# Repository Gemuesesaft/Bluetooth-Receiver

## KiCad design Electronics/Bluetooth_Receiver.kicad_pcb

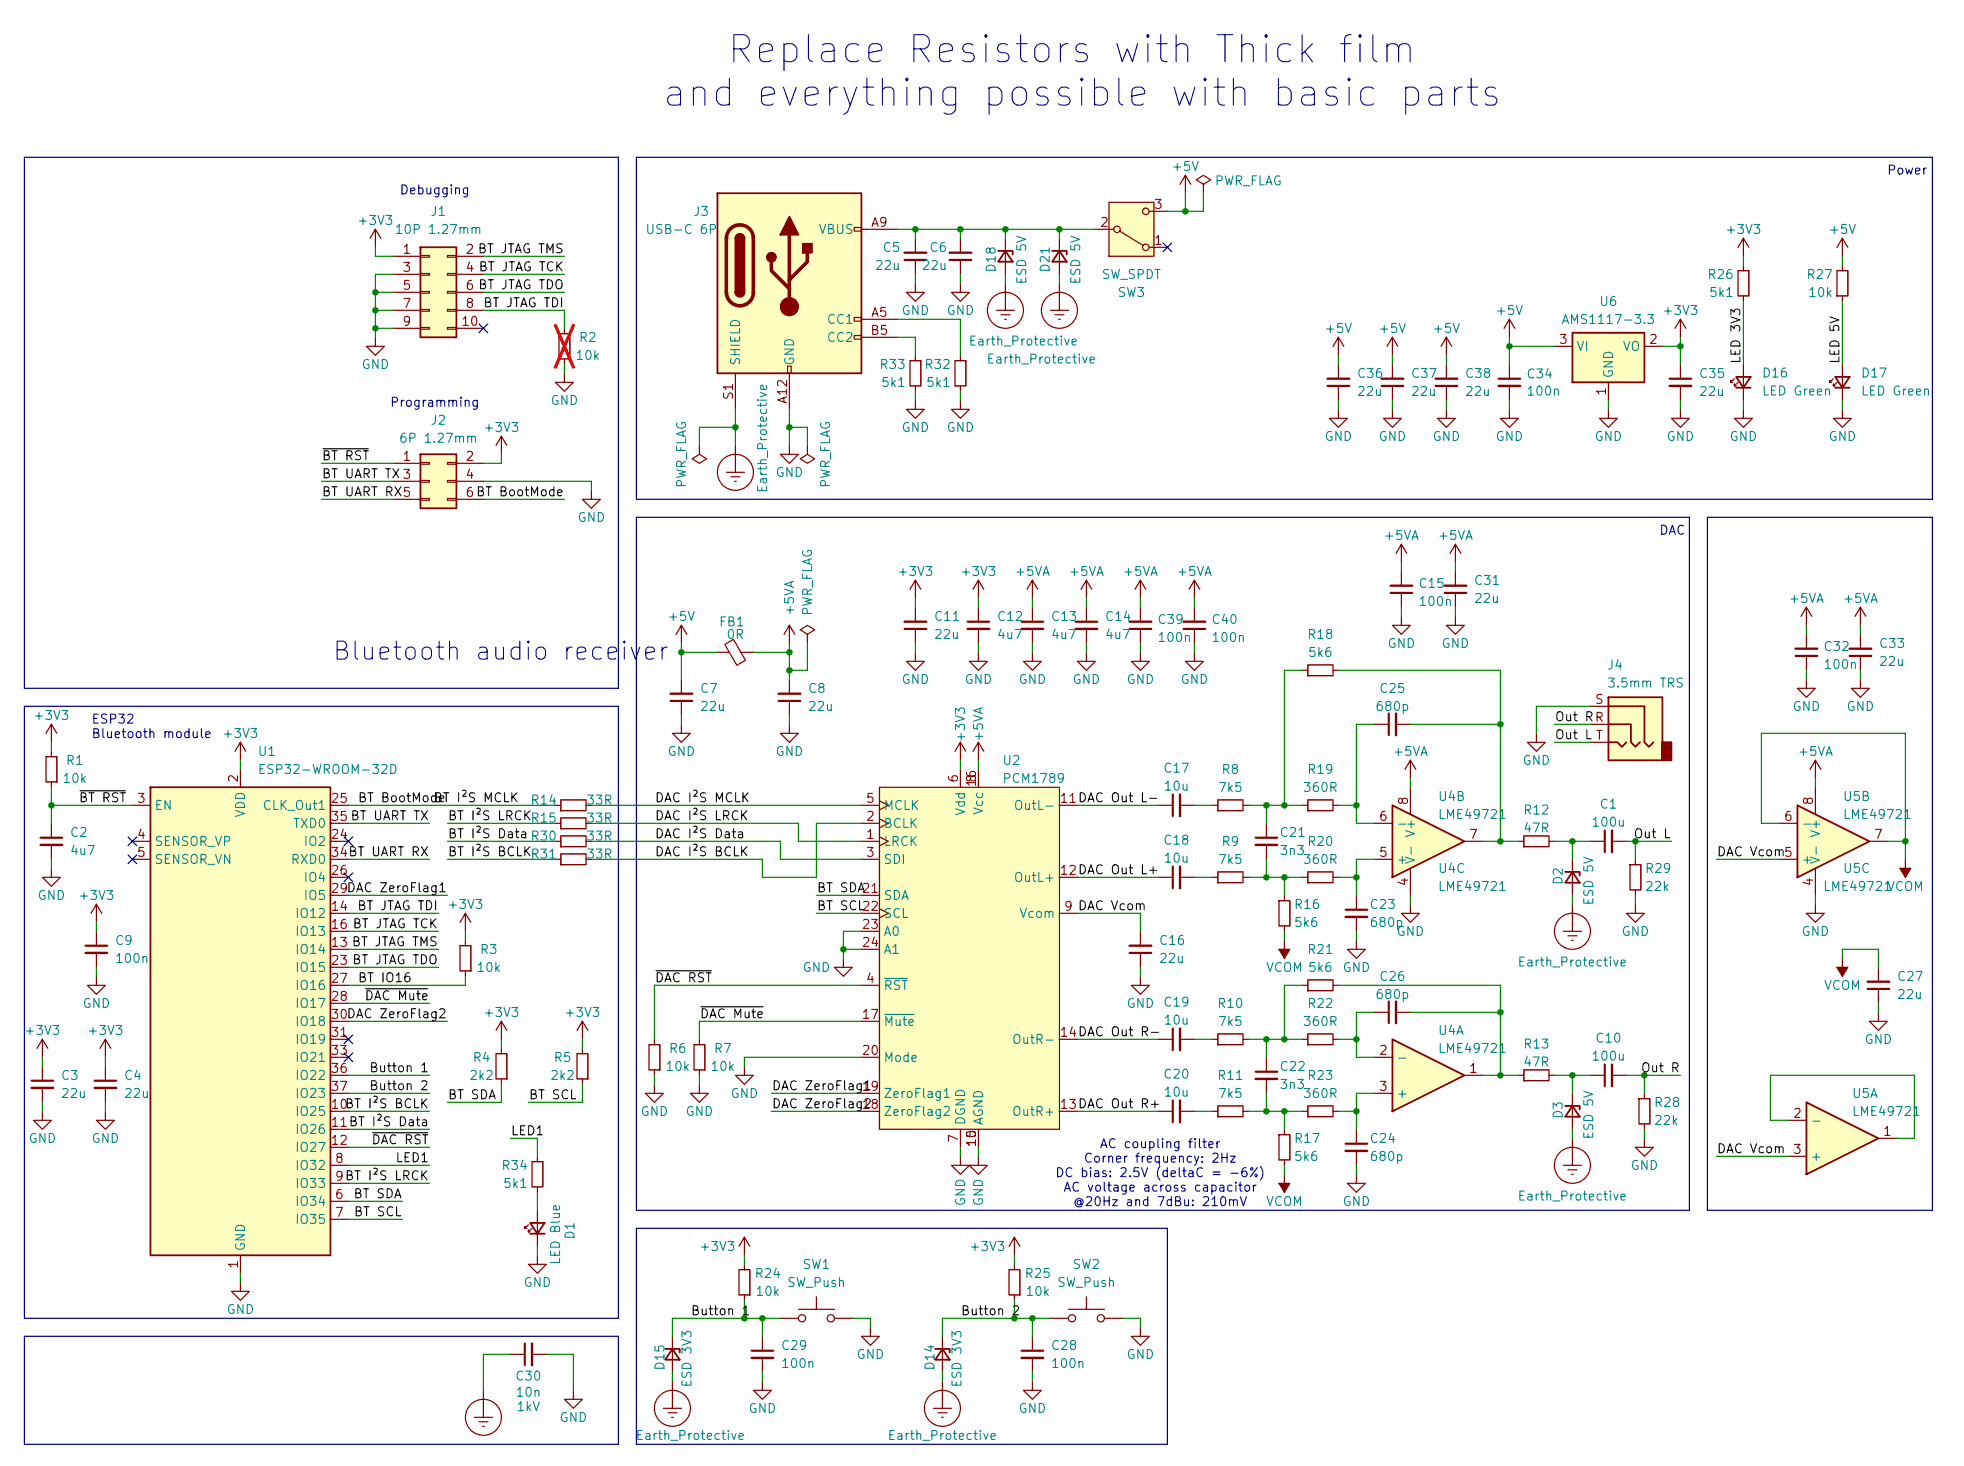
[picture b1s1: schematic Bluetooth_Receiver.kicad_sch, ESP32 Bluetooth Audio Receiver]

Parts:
C1, C10: 100u; C_1206_3216Metric; Rated Voltage 6V3; Tolerance 20%; Manufacturer Part # CL31A107MQHNNNE; JLCPCB Part # C15008
C2, C12, C13, C14: 4u7; C_0805_2012Metric; Rated Voltage 25V; Tolerance 10%; Manufacturer Part # CL21A475KAQNNNE; JLCPCB Part # C1779
C3, C4, C5, C6, C7, C8, C11, C16, C27, C31, C33, C35, C36, C37, C38: 22u; C_0805_2012Metric; Rated Voltage 25V; Tolerance 20%; Manufacturer Part # CL21A226MAQNNNE; JLCPCB Part # C45783
C9, C15, C28, C29, C32, C34, C39, C40: 100n; C_0603_1608Metric; Rated Voltage 50V; Tolerance 10%; Manufacturer Part # CC0603KRX7R9BB104; JLCPCB Part # C14663
C17, C18, C19, C20: 10u; C_1206_3216Metric; Rated Voltage 50V; Tolerance 10%; Manufacturer Part # CL31A106KBHNNNE; JLCPCB Part # C13585
C21, C22: 3n3; C_0603_1608Metric; Rated Voltage 50V; Tolerance 5%; Manufacturer Part # GRM1885C1H332JA01D; JLCPCB Part # C77036
C23, C24, C25, C26: 680p; C_0603_1608Metric; Rated Voltage 50V; Tolerance 5%; Manufacturer Part # CGA3E2C0G1H681JT0Y0N; JLCPCB Part # C342925
C30: 10n; C_1206_3216Metric; Rated Voltage 1kV; Manufacturer Part # 1206B103K102NT; JLCPCB Part # C9194
D1: LED Blue; LED_0805_2012Metric; Manufacturer Part # 17-21/BHC-AL2M2TY/3T; JLCPCB Part # C94613
D2, D3, D18, D21: ESD 5V; D_SOD-882; Manufacturer Part # ESD9X5.0ST5G-ES; JLCPCB Part # C19170850
D14, D15: ESD 3V3; D_SOD-523; Manufacturer Part # ESD5Z3.3; JLCPCB Part # C475684
D16, D17: LED Green; LED_0805_2012Metric; Manufacturer Part # KT-0805G; JLCPCB Part # C2297
FB1: 0R; L_0603_1608Metric; Tolerance 50mΩ; Manufacturer Part # 0603WAF0000T5E; JLCPCB Part # C21189
J1: 10P 1.27mm; PinHeader_2x05_P1.27mm_Horizontal; Manufacturer Part # 1271WR-2x5P; JLCPCB Part # C7470108
J2: 6P 1.27mm; PinHeader_2x03_P1.27mm_Horizontal; Manufacturer Part # 1271WR-2x3P; JLCPCB Part # C7470106
J3: USB-C 6P; USB_C_Receptacle_HRO_TYPE-C-31-M-17; Manufacturer Part # HC-TYPE-C-6P-01A; JLCPCB Part # C2894893
J4: 3.5mm TRS; Jack_3.5mm_CUI_SJ-3523-SMT_Horizontal; Manufacturer Part # PJ-320-3P SMT; JLC Basic Part No
R1, R3, R6, R7, R24, R25, R27: 10k; R_0402_1005Metric; Rated Voltage 50V; Tolerance 1%; Manufacturer Part # 0402WGF1002TCE; JLCPCB Part # C25744
R2: 10k; R_0402_1005Metric; Rated Voltage 50V; Tolerance 1%; Manufacturer Part # 0402WGF1002TCE; JLCPCB Part # C25744; not fitted
R4, R5: 2k2; R_0402_1005Metric; Rated Voltage 50V; Tolerance 1%; Manufacturer Part # 0402WGF2201TCE; JLCPCB Part # C25879
R8, R9, R10, R11: 7k5; R_0805_2012Metric; Rated Voltage 150V; Tolerance 0.1%; Manufacturer Part # RT0805BRD077K5L; JLCPCB Part # C136918
R12, R13: 47R; R_0805_2012Metric; Rated Voltage 150V; Tolerance 1%; Manufacturer Part # 0805W8F470JT5E; JLCPCB Part # C17714
R14, R15, R30, R31: 33R; R_0402_1005Metric; Rated Voltage 50V; Tolerance 1%; Manufacturer Part # 0402WGF330JTCE; JLCPCB Part # C25105
R16, R17, R18, R21: 5k6; R_0805_2012Metric; Rated Voltage 100V; Tolerance 0.1%; Manufacturer Part # ERA6AEB562V; JLCPCB Part # C445654
R19, R20, R22, R23: 360R; R_0805_2012Metric; Rated Voltage 150V; Tolerance 0.1%; Manufacturer Part # RT0805BRD07360RL; JLCPCB Part # C865427
R26, R32, R33, R34: 5k1; R_0603_1608Metric; Rated Voltage 50V; Tolerance 1%; Manufacturer Part # 0603WAF5101T5E; JLC Basic Part Yes
R28, R29: 22k; R_0402_1005Metric; Rated Voltage 50V; Tolerance 1%; Manufacturer Part # 0402WGF2202TCE; JLCPCB Part # C25768
SW1, SW2: SW_Push; SKMP; Manufacturer Part # SKPMBHE010; JLCPCB Part # C115350
SW3: SW_SPDT; SW_Slide-03_Wuerth-WS-SLTV_10x2.5x6.4_P2.54mm; Manufacturer Part # SS-12D01-G5; JLC Basic Part No
U1: ESP32-WROOM-32D; Manufacturer Part # ESP32-WROOM-32D-H4; JLCPCB Part # C3013936
U2: PCM1789; TSSOP-24_4.4x7.8mm_P0.65mm; Manufacturer Part # PCM1789PWR; JLCPCB Part # C962089
U4, U5: LME49721; SOIC-8_3.9x4.9mm_P1.27mm; Manufacturer Part # LME49721MAX/NOPB; JLCPCB Part # C129347
U6: AMS1117-3.3; SOT-223-3_TabPin2; Manufacturer Part # AMS1117-3.3; JLC Basic Part Yes

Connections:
+3V3: C3.1, C4.1, C9.1, C11.2, C12.1, C35.1, J1.1, J2.2, R1.2, R3.2, R4.2, R5.2, R24.2, R25.2, R26.1, U1.2 (VDD), U2.6 (Vdd), U6.2 (VO)
+5V: C7.2, C34.1, C36.2, C37.2, C38.2, FB1.1, R27.2, SW3.3 (C), U6.3 (VI)
+5VA: C8.2, C13.1, C14.1, C15.2, C31.2, C32.2, C33.2, C39.2, C40.2, FB1.2, U2.8 (Vcc), U2.16 (Vcc), U4.8 (V+), U5.8 (V+)
/BT BootMode: J2.6, R14.1, U1.25 (CLK_Out1)
/BT IO16: R3.1, U1.27 (IO16)
/BT I²S BCLK: R31.1, U1.10 (IO25)
/BT I²S Data: R30.1, U1.11 (IO26)
/BT I²S LRCK: R15.1, U1.9 (IO33)
/BT JTAG TCK: J1.4, U1.16 (IO13)
/BT JTAG TDI: J1.8, R2.2, U1.14 (IO12)
/BT JTAG TDO: J1.6, U1.23 (IO15)
/BT JTAG TMS: J1.2, U1.13 (IO14)
/BT SCL: R5.1, U1.7 (IO35), U2.22 (SCL)
/BT SDA: R4.1, U1.6 (IO34), U2.21 (SDA)
/BT UART RX: J2.5, U1.34 (RXD0)
/BT UART TX: J2.3, U1.35 (TXD0)
/Button 1: C29.1, D15.1 (K), R24.1, SW1.1, U1.36 (IO22)
/Button 2: C28.1, D14.1 (K), R25.1, SW2.1, U1.37 (IO23)
/DAC I²S BCLK: R31.2, U2.2 (BCLK)
/DAC I²S Data: R30.2, U2.3 (SDI)
/DAC I²S LRCK: R15.2, U2.1 (LRCK)
/DAC I²S MCLK: R14.2, U2.5 (MCLK)
/DAC Out L+: C18.1, U2.12 (OutL+)
/DAC Out L-: C17.1, U2.11 (OutL-)
/DAC Out R+: C20.1, U2.13 (OutR+)
/DAC Out R-: C19.1, U2.14 (OutR-)
/DAC Vcom: C16.2, U2.9 (Vcom), U5.3 (+), U5.5 (+)
/DAC ZeroFlag1: U1.29 (IO5), U2.19 (ZeroFlag1)
/DAC ZeroFlag2: U1.30 (IO18), U2.18 (ZeroFlag2)
/LED1: R34.1, U1.8 (IO32)
/LED 3V3: D16.2 (A), R26.2
/LED 5V: D17.2 (A), R27.1
/Out L: C1.2, J4.T, R29.1
/Out R: C10.2, J4.R, R28.1
/~BT RST: C2.1, J2.1, R1.1, U1.3 (EN)
/~DAC Mute: R7.2, U1.28 (IO17), U2.17 (~Mute)
/~DAC RST: R6.2, U1.12 (IO27), U2.4 (~RST)
Earth_Protective: C30.1, D2.2 (A), D3.2 (A), D14.2 (A), D15.2 (A), D18.2 (A), D21.2 (A), J3.S1 (SHIELD)
GND: C2.2, C3.2, C4.2, C5.1, C6.1, C7.1, C8.1, C9.2, C11.1, C12.2, C13.2, C14.2, C15.1, C16.1, C23.2, C24.2, C27.1, C28.2, C29.2, C30.2, C31.1, C32.1, C33.1, C34.2, C35.2, C36.1, C37.1, C38.1, C39.1, C40.1, D1.1 (K), D16.1 (K), D17.1 (K), J1.3, J1.5, J1.7, J1.9, J2.4, J3.A12 (GND), J3.B12 (GND), J4.S, R2.1, R6.1, R7.1, R28.2, R29.2, R32.2, R33.2, SW1.2, SW2.2, U1.1 (GND), U1.15 (GND), U1.38 (GND), U1.39 (GND), U2.7 (DGND), U2.10 (AGND), U2.15 (AGND), U2.20 (Mode), U2.23 (A0), U2.24 (A1), U4.4 (V-), U5.4 (V-), U6.1 (GND)
unnamed: C17.2, R8.1
unnamed: C18.2, R9.1
unnamed: C19.2, R10.1
unnamed: C20.2, R11.1
unnamed: C21.1, R8.2, R18.1, R19.1
unnamed: C21.2, R9.2, R16.1, R20.1
unnamed: C22.1, R10.2, R21.1, R22.1
unnamed: C22.2, R11.2, R17.1, R23.1
unnamed: C25.2, R12.1, R18.2, U4.7
unnamed: C26.2, R13.1, R21.2, U4.1
unnamed: D1.2 (A), R34.2
unnamed: C1.1, D2.1 (K), R12.2
unnamed: C10.1, D3.1 (K), R13.2
unnamed: C5.2, C6.2, D18.1 (K), D21.1 (K), J3.A9 (VBUS), J3.B9 (VBUS), SW3.2 (B)
unnamed: J3.A5 (CC1), R32.1
unnamed: J3.B5 (CC2), R33.1
unnamed: C24.1, R23.2, U4.3 (+)
unnamed: C26.1, R22.2, U4.2 (-)
unnamed: C23.1, R20.2, U4.5 (+)
unnamed: C25.1, R19.2, U4.6 (-)
unnamed: U5.1, U5.2 (-)
VCOM: C27.2, R16.2, R17.2, U5.6 (-), U5.7

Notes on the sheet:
AC coupling filter Corner frequency: 2Hz DC bias: 2.5V (deltaC = -6%) AC voltage across capacitor @20Hz and 7dBu: 210mV
Replace Resistors with Thick film and everything possible with basic parts
ESP32 Bluetooth module
DAC
Programming
Debugging
Bluetooth audio receiver
Power

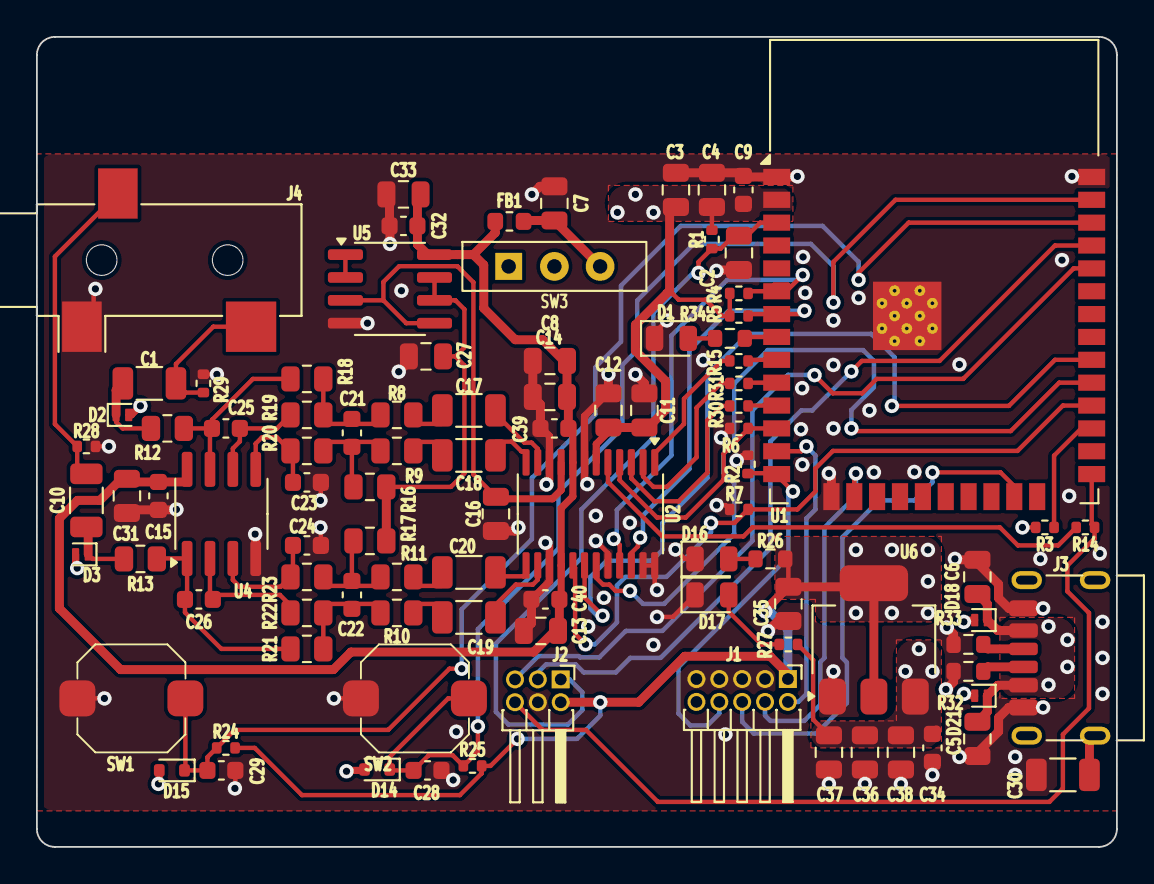
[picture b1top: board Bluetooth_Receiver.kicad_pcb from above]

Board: 4 copper layers, 60.0 x 45.0 mm, 96 parts (0 on the bottom side), 61 nets.

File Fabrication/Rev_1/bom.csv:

Designator,Footprint,Quantity,Value,LCSC Part #
"C1, C10",1206,2,100u,C15008
"C11, C16, C27, C3, C31, C33, C35, C36, C37, C38, C4, C5, C6, C7, C8",0805,15,22u,C45783
"C12, C13, C14, C2",0805,4,4u7,C1779
"C15, C28, C29, C32, C34, C39, C40, C9",0603,8,100n,C14663
"C17, C18, C19, C20",1206,4,10u,C13585
"C21, C22",0603,2,3n3,C77036
"C23, C24, C25, C26",0603,4,680p,C342925
C30,1206,1,10n,C9194
D1,0805,1,LED Blue,C94613
"D14, D15",D_SOD-523,2,ESD 3V3,C475684
"D16, D17",0805,2,LED Green,C2297
"D18, D2, D21, D3",D_SOD-882,4,ESD 5V,C19170850
FB1,0603,1,0R,C21189
J1,PinHeader_2x05_P1.27mm_Horizontal,1,10P 1.27mm,C7470108
J2,PinHeader_2x03_P1.27mm_Horizontal,1,6P 1.27mm,C7470106
J3,USB_C_Receptacle_HRO_TYPE-C-31-M-17,1,USB-C 6P,C2894893
J4,Jack_3.5mm_CUI_SJ-3523-SMT_Horizontal,1,3.5mm TRS,C17701688
"R1, R24, R25, R27, R3, R6, R7",0402,7,10k,C25744
"R10, R11, R8, R9",0805,4,7k5,C136918
"R12, R13",0805,2,47R,C17714
"R14, R15, R30, R31",0402,4,33R,C25105
"R16, R17, R18, R21",0805,4,5k6,C445654
"R19, R20, R22, R23",0805,4,360R,C865427
"R26, R32, R33, R34",0603,4,5k1,C23186
"R28, R29",0402,2,22k,C25768
"R4, R5",0402,2,2k2,C25879
"SW1, SW2",SKMP,2,SW_Push,C115350
SW3,SW_Slide-03_Wuerth-WS-SLTV_10x2.5x6.4_P2.54mm,1,SW_SPDT,C2998805
U1,ESP32-WROOM-32D,1,ESP32-WROOM-32D,C3013936
U2,TSSOP-24_4.4x7.8mm_P0.65mm,1,PCM1789,C962089
"U4, U5",SOIC-8_3.9x4.9mm_P1.27mm,2,LME49721,C129347
U6,SOT-223-3_TabPin2,1,AMS1117-3.3,C6186

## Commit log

2025-04-30 Initial Commit.
2025-04-30 Removes unused footprints.
